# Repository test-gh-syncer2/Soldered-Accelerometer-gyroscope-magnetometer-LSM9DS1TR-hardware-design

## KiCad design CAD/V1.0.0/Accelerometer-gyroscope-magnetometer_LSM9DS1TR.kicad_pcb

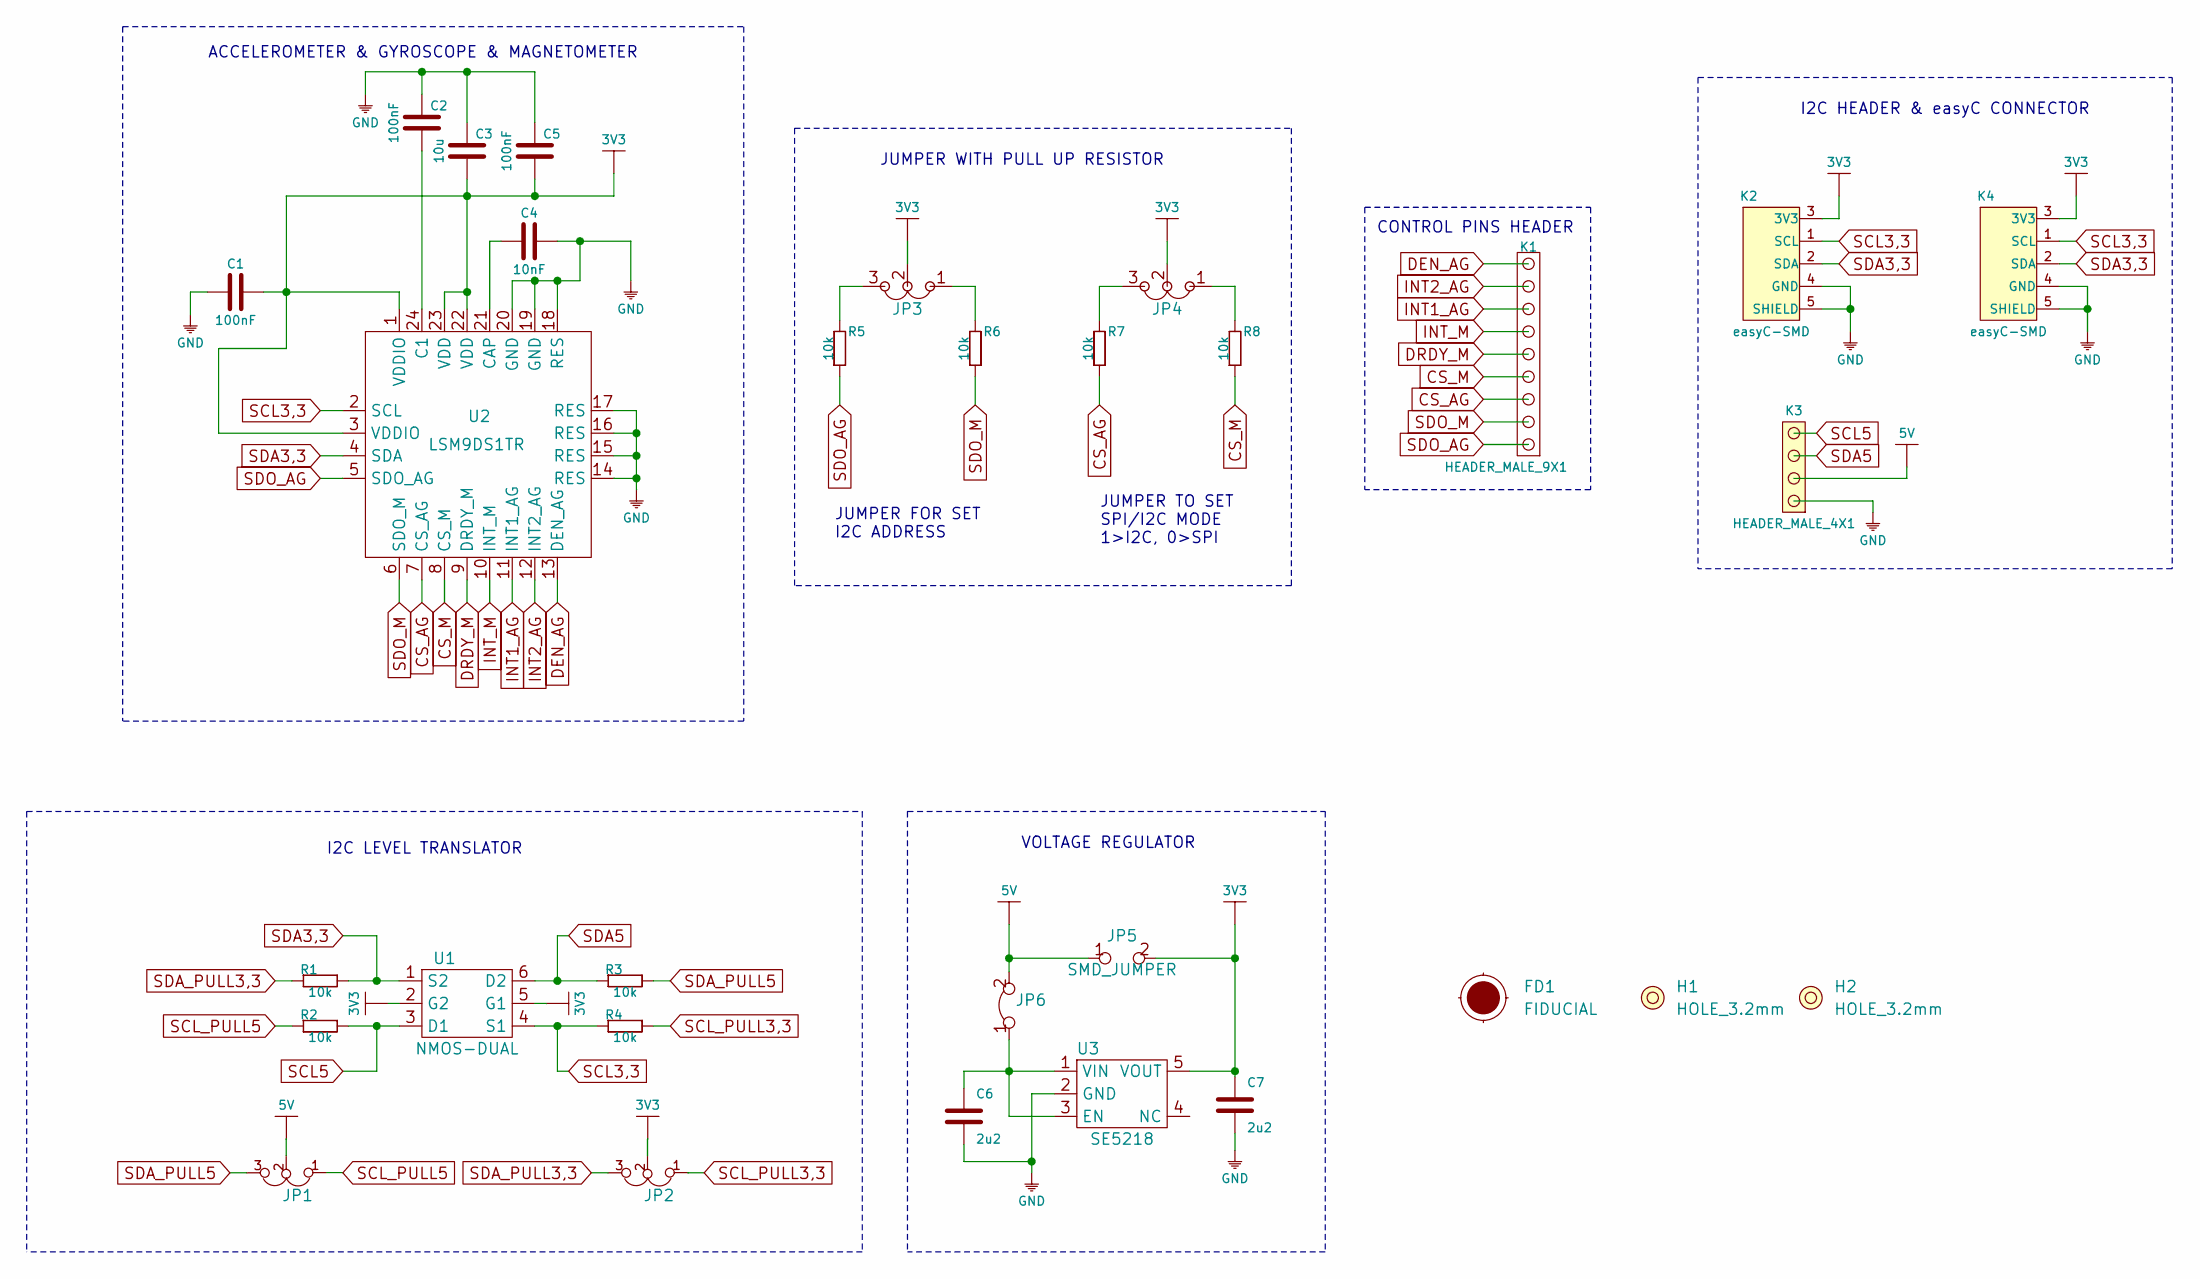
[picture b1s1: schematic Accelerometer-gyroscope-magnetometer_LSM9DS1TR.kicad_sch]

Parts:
C1, C2, C5: 100nF; 0603C
C3: 10u; 1206C
C4: 10nF; 0603C
C6, C7: 2u2; 0603C
FD1: FIDUCIAL; FIDUCIAL_23
H1, H2: HOLE_3.2mm
JP1, JP2, JP3, JP4: SMD_JUMPER_3_PAD_TRACE
JP5: SMD_JUMPER
JP6: SMD-JUMPER-CONNECTED_TRACE_SLODERMASK
K1: HEADER_MALE_9X1
K2, K4: easyC-SMD; easyC-connector
K3: HEADER_MALE_4X1
R1, R2, R3, R4, R5, R6, R7, R8: 10k; 0603R
U1: NMOS-DUAL; SOT-363
U2: LSM9DS1TR
U3: SE5218; SOT-23-5

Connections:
3V3: C1.2, C3.1, C5.2, C7.2, JP2.2, JP3.2, JP4.2, JP5.2, K2.3 (3V3), K4.3 (3V3), U1.2 (G2), U1.5 (G1), U2.1 (VDDIO), U2.3 (VDDIO), U2.22 (VDD), U2.23 (VDD), U3.5 (VOUT)
5V: JP1.2, JP5.1, JP6.2, K3.2
CS_AG: K1.3, R7.1, U2.7 (CS_AG)
CS_M: K1.4, R8.1, U2.8 (CS_M)
DEN_AG: K1.9, U2.13 (DEN_AG)
DRDY_M: K1.5, U2.9 (DRDY_M)
GND: C1.1, C2.2, C3.2, C4.2, C5.1, C6.1, C7.1, K2.4 (GND), K2.5 (SHIELD), K3.1, K4.4 (GND), K4.5 (SHIELD), U2.14 (RES), U2.15 (RES), U2.16 (RES), U2.17 (RES), U2.18 (RES), U2.19 (GND), U2.20 (GND), U3.2 (GND)
INT1_AG: K1.7, U2.11 (INT1_AG)
INT2_AG: K1.8, U2.12 (INT2_AG)
INT_M: K1.6, U2.10 (INT_M)
unnamed: C2.1, U2.24 (C1)
unnamed: C4.1, U2.21 (CAP)
unnamed: C6.2, JP6.1, U3.1 (VIN), U3.3 (EN)
unnamed: JP3.1, R6.2
unnamed: JP3.3, R5.2
unnamed: JP4.1, R8.2
unnamed: JP4.3, R7.2
SCL3,3: K2.1 (SCL), K4.1 (SCL), R4.1, U1.4 (S1), U2.2 (SCL)
SCL5: K3.4, R2.2, U1.3 (D1)
SCL_PULL3,3: JP2.1, R4.2
SCL_PULL5: JP1.1, R2.1
SDA3,3: K2.2 (SDA), K4.2 (SDA), R1.2, U1.1 (S2), U2.4 (SDA)
SDA5: K3.3, R3.1, U1.6 (D2)
SDA_PULL3,3: JP2.3, R1.1
SDA_PULL5: JP1.3, R3.2
SDO_AG: K1.1, R5.1, U2.5 (SDO_AG)
SDO_M: K1.2, R6.1, U2.6 (SDO_M)

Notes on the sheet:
ACCELEROMETER & GYROSCOPE & MAGNETOMETER
I2C LEVEL TRANSLATOR
JUMPER FOR SET I2C ADDRESS
JUMPER WITH PULL UP RESISTOR
VOLTAGE REGULATOR
JUMPER TO SET SPI/I2C MODE 1>I2C, 0>SPI
CONTROL PINS HEADER
I2C HEADER & easyC CONNECTOR

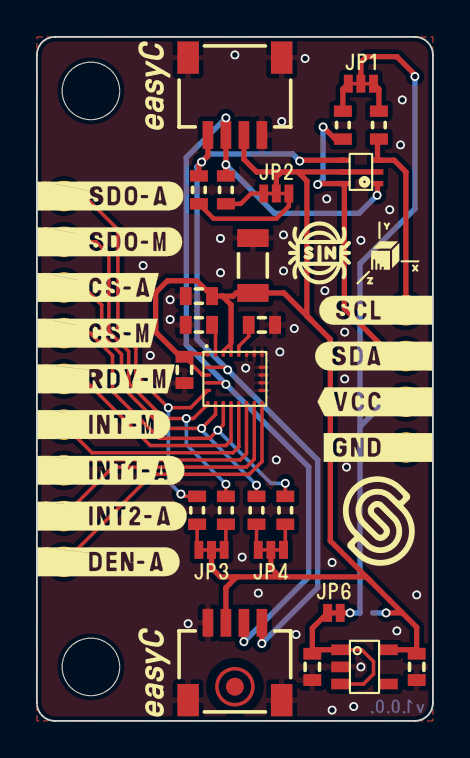
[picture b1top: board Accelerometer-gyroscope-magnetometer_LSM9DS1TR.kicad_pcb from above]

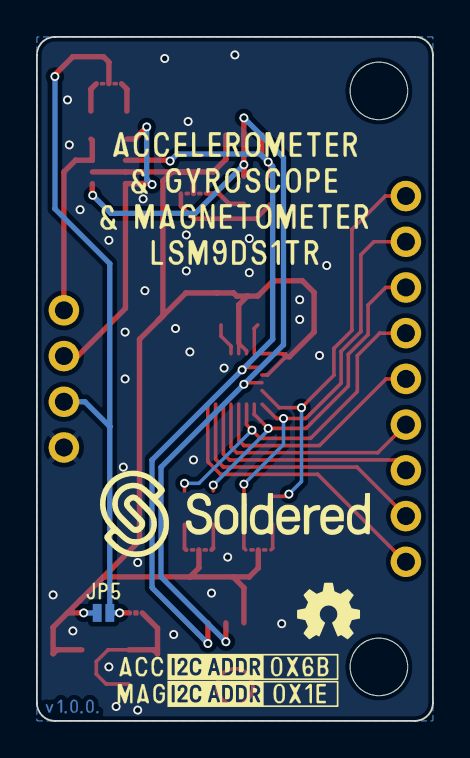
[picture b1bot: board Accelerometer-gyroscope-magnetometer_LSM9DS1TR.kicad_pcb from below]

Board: 2 copper layers, 22.0 x 38.0 mm, 32 parts (2 on the bottom side), 27 nets.

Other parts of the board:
Ref**: Val**; Version1.0.0.

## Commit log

2021-09-23 Syncing to git
2021-09-23 Updating open source files.
